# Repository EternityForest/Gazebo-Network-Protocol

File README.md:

Gazebo-Network-Protocol
=======================

A very simple network protocol for self documenting devices supporting natve error handling, 
units of measure, device discovery, and many other features.

Gazebo allows plug and play devices to expose "Parameters" to a master device.
Parameters are not limited to simple variables and may represent arrays, item or message oriented FIFO buffers, or 
even function calls.

Devices are uniquely identified with UUIDs allowing anyone to create conforming device by randomly generating the UUID
rather than purchase a number from some authority.

The code currently comiles to under 9k on the arduino leonardo. All the hardware dependant stuff is in one small file so
it is very easy to port.

Dependancies
------------
Python(tested on 3.xx, may work in 2.6+)

crcmod

pyserial

Creating Slave Devices
----------------------
Look at the example arduino sketch, particularly networkinterface.c and machine.cpp.
The implementation was designed so that those are the only files that you need to modify.

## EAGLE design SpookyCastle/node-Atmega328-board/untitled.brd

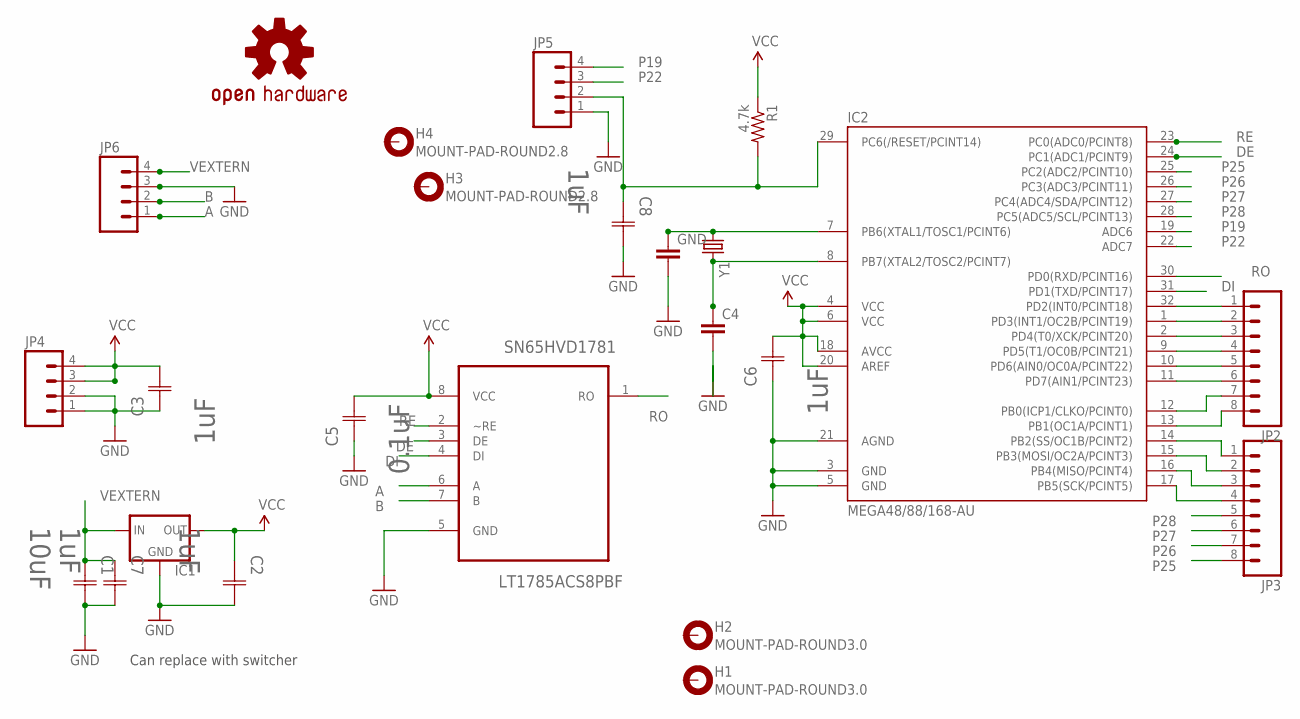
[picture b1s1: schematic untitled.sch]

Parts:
C1: 10uF; CAPC3225X270N
C2: 1uF; CAPC2013X135N
C3, C6, C7, C8: 1uF; CAPC2013X135N; TOLERANCE ±10%; VOLTAGERATING 50V; MPN GRM21BR71H105KA12L
C4: CAP0805; 0805
C5: 0.1uF; CAPC2013X135N; TOLERANCE ±10%; VOLTAGERATING 50V; MPN GRM21BR71H105KA12L
GND: CAP0805; 0805
H1, H2: MOUNT-PAD-ROUND3.0; 3,0-PAD
H3, H4: MOUNT-PAD-ROUND2.8; 2,8-PAD
IC1: V_REG_78XXSIDE; 78XXL
IC2: MEGA48/88/168-AU; TQFP32-08
JP2, JP3: M08LOCK; 1X08_LOCK
JP4: M04PTH; 1X04
JP5: M04LOCK; 1X04_LOCK
JP6: M04SCREW; SCREWTERMINAL-3.5MM-4
R1: 4.7k; 0805
SN65HVD1781: LT1785ACS8PBF; SOIC127P600X175-8N
U$1: OSHW-LOGOM; OSHW-LOGO-M
Y1: CRYSTALSMD; HC49UP

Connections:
A: JP6.1, SN65HVD1781.6 (A)
B: JP6.2, SN65HVD1781.7 (B)
DE: IC2.24 (PC1(ADC1/PCINT9)), SN65HVD1781.3 (DE)
DI: IC2.31 (PD1(TXD/PCINT17)), SN65HVD1781.4 (DI)
GND: C1.2 (C2), C2.2 (C2), C3.1 (C1), C4.2, C5.1 (C1), C6.1 (C1), C7.2 (C2), C8.2 (C2), GND.2, IC1.GND, IC2.3 (GND), IC2.5 (GND), IC2.21 (AGND), JP4.1, JP4.2, JP5.1, JP6.3, SN65HVD1781.5 (GND)
unnamed: IC2.32 (PD2(INT0/PCINT18)), JP2.1
unnamed: IC2.1 (PD3(INT1/OC2B/PCINT19)), JP2.2
unnamed: IC2.2 (PD4(T0/XCK/PCINT20)), JP2.3
unnamed: IC2.9 (PD5(T1/OC0B/PCINT21)), JP2.4
unnamed: IC2.10 (PD6(AIN0/OC0A/PCINT22)), JP2.5
unnamed: IC2.11 (PD7(AIN1/PCINT23)), JP2.6
unnamed: IC2.12 (PB0(ICP1/CLKO/PCINT0)), JP2.7
unnamed: IC2.13 (PB1(OC1A/PCINT1)), JP2.8
unnamed: IC2.14 (PB2(SS/OC1B/PCINT2)), JP3.1
unnamed: IC2.15 (PB3(MOSI/OC2A/PCINT3)), JP3.2
unnamed: IC2.16 (PB4(MISO/PCINT4)), JP3.3
unnamed: IC2.17 (PB5(SCK/PCINT5)), JP3.4
unnamed: GND.1, IC2.7 (PB6(XTAL1/TOSC1/PCINT6)), Y1.1
unnamed: C4.1, IC2.8 (PB7(XTAL2/TOSC2/PCINT7)), Y1.2
unnamed: C8.1 (C1), IC2.29 (PC6(/RESET/PCINT14)), JP5.2, R1.2
P19: IC2.19 (ADC6), JP5.4
P22: IC2.22 (ADC7), JP5.3
P25: IC2.25 (PC2(ADC2/PCINT10)), JP3.8
P26: IC2.26 (PC3(ADC3/PCINT11)), JP3.7
P27: IC2.27 (PC4(ADC4/SDA/PCINT12)), JP3.6
P28: IC2.28 (PC5(ADC5/SCL/PCINT13)), JP3.5
RE: IC2.23 (PC0(ADC0/PCINT8)), SN65HVD1781.2 (~RE)
RO: IC2.30 (PD0(RXD/PCINT16)), SN65HVD1781.1 (RO)
VCC: C2.1 (C1), C3.2 (C2), C5.2 (C2), C6.2 (C2), IC1.OUT, IC2.4 (VCC), IC2.6 (VCC), IC2.18 (AVCC), IC2.20 (AREF), JP4.3, JP4.4, R1.1, SN65HVD1781.8 (VCC)
VEXTERN: C1.1 (C1), C7.1 (C1), IC1.IN, JP6.4

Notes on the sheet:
Can replace with switcher

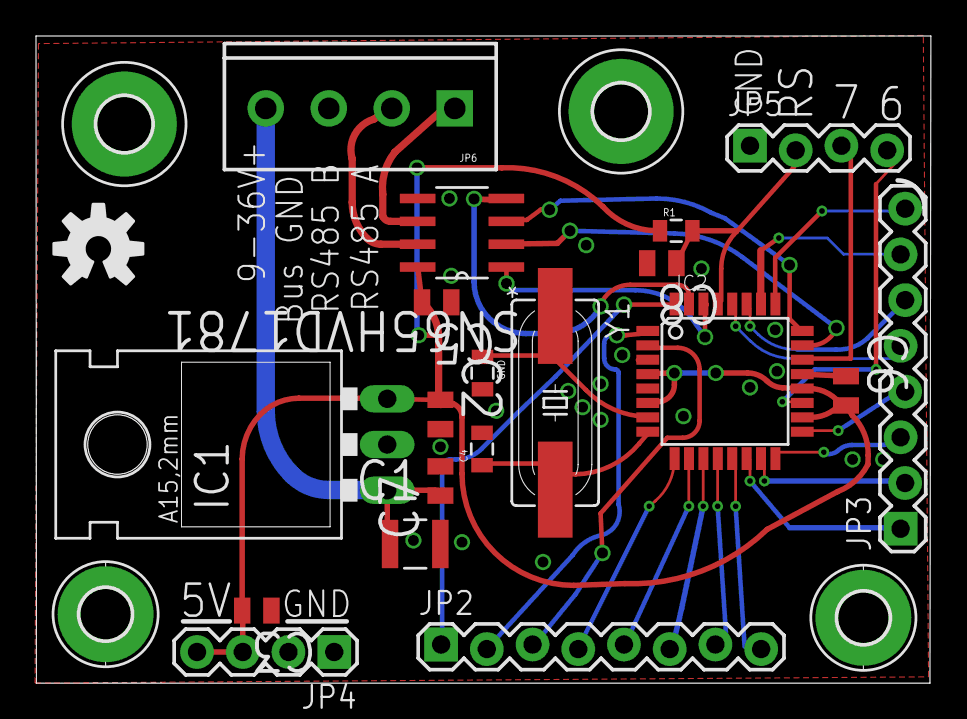
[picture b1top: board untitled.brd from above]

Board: 2 copper layers, 49.7 x 36.0 mm, 24 parts (0 on the bottom side), 30 nets.

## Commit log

2013-02-19 First commit with actual code.
2013-02-19 Added readme for python library, edited readme.
2013-02-19 Added more python documentation, changed readme.
2013-02-19 I let zim add its folder to the repo so that all the text can be in zim's format and easily converted to HTML, etc.
    A bit odd, but it works for a project so dependant on formal documentation.
2013-02-20 Core protocol version 0.11: Changes: Added language clarifying that backwards compatibility with past versions does not become a priorty until version 1.0 of the core protocol.
    Added license text: LGPL for code and CC-BY-SA for documentation
    Added a copy of the LGPL and GPL version 3
    Added a misc directory for the spinoff projects currently containing a
    spreadsheet with some cool electronics calculators and an openoffice
    template for documentation(zim is still the primary documentation editor)
2013-02-21 Refactored the translation layer between python and gazebo data, enums and strings now supported, added a few "unit tests" really just a file that counts failures when trying known answer tests.
    Implemented __repr__ for Gazebo_Slave class
2013-02-22 Changed core protocol. enum ; delimented. S;ave descriptor changed. Added information broadcast capability to thr reference implementation. NV save still not working. Added more unit tests. Fixed a b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
    Added a read with arguments parameter to the slave.
    Refactored the slave interface files just a bit.
2013-02-25 Core protocol changes Changed enum separater to | added void type Improved runtime checking in the slave
    Changed a function in the slave lib to deal with null strings properly
    can use number for enum val
    added test sketch SpookyCastle, a generic i/o board
    Got rid of the old test sketch
    reorganized things a bit
2013-02-25 Forgot to change the name in the import statemet when i changed the python library file name.
2013-02-25 Properly flagged any params in SpookyCastle that have side effects.
2013-02-25 flagged params with side effects in SpookyCastle
2013-02-26 Clarified the mechanism behind baud rate set messages(core protocol to version 0.33) Added a setup.py file(nothing fancy)
2013-02-26 Got rid of ODS lock file of the spreadsheet. Got rid of the build directory, it only takes like 2 seconds to build.
2013-02-26 The self.comport.flush was not doing what i thought it did with some versions and was infact breaking everything.
2013-02-26 small fixes
2013-02-27 Order of magnitude speed improvement by avoiding changing the serial port timeout so often.
2013-03-05 Added a very slow pool of dubious entropy to the spookycastle code. It generates about 1 byte per second but is a cool demo. The entropy is distilled by the XABC pseudorandom number generator from se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
2013-03-05 Core Protocol to version 0.4.4: Changed versioning scheme, deprecated a few redundant datatypes,
    Fixed a bug involving variable arrays.
    Added a PDF version of the specification.
2013-03-06 Core protocol version 0.5.5: Changed requirements for physical layer: Devices should now tolerate a fault of 37V to eithr rs485 line, and the working voltage is now 24V. Devices must survive a contin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
    Looser hot plug requirements: 30uH+2Ohm and 300uH+20Ohm. Theese are worse than
    worst case values for 100ft + 1000ft of 22 gauge wire.
    Also, modified the standard template so that headers with borders don't merge
    with the next border in the ugly way they were.
2013-03-07 Core protocol to version 0.6.5, added changelog. The big new thing is that tuples are supported as parameter types!
2013-03-08 Added a support for write without confirmation in pygazebo. Reorganized SpookyCastle, started working on an atmega board.
2013-03-11 Almost finished with the SpookyCastle atmega board, core protocol version 0.7.6: Pin ordering changed for rs485, updated PDF.
2013-03-11 Almost done making SpookyCastle board fit in 5cmx5cm
2013-03-12 Added option for 1210 capacitor on input of vreg, mitered some noise critical routing.
2013-03-13 Added option for bigger capacitor.
2013-03-13 Added a buncha silk to the board.
2013-03-20 see changelog.
2013-03-20 Updated board and spec pdf. PDF is all bold due to what I think is an OpenOffice bug.
2013-03-20 Fixed some formatting issues in the spreadsheet fixed a nonsensical comment.
2013-03-22 Adds wire data to the spreadsheet
2013-03-22 Fix critical silk error(Text on wrong side) Add HTML version of the spec since OO is outputting all bold PDFs
2013-03-25 Added watts to dbm and dbm to wats to the spreadsheet
2013-04-02 Added plate capacitor calc, inductor and capacitor impedence calc.
2013-04-03 Protocol Version 0.8.7: Scope no loer includes power or connectors, added predefined group classes.
2013-04-03 Updated the spookycastle board to use screw terminals since the spec no longer requires rj11
2013-04-15 Added gerber files for the SpookCastle node board. Please note that these are untested, testing will happen when the boards come back from china.
2013-04-16 the python master implementation can now cache the results of Idempotent function calls as long as they dont have side effects.
2013-06-27 Made networl thread a daemon
2013-07-04 Changed build process. OpenOffice primary editor, changelog now stored as metadata in the ODT file
2013-07-18 whole buncha changes

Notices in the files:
parts and their libraries:
SparkFun - Copy: Licensing: CC v3.0 Share-Alike You are welcome to use this library for commercial purposes.
